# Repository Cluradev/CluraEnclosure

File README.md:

# CluraEnclosure

**The Clura Enclosure** is the 100% open-source, modular, and smart enclosure designed for desktop 3D printers. Developed with a focus on safety and air quality, it incorporates active filtration and smart sensors to enhance your 3D printing experience.

[Discord Community](https://discord.gg/dJDUmdvcgZ)

## Why We Built It

The project started with me (Fabrizio), an aerospace engineering student who wanted to print in his room without compromising his safety. In fact, it is widely documented that most 3D printer filaments emit VOCs and particulate matter, which can be harmful to health. I searched for a smart, affordable, open-source enclosure but couldn't find one, so I decided to build my own. 18 months of hard work later, here we are!

## Kits

Kickstarter orders are being fulfilled. Future kit batches are being planned, but nothing is finalized yet.

You can still build the enclosure today without waiting on us. Everything here is open source and the [Bill of Materials](Documentation/README.md) lists every part with soemtimes supplier links.

The original campaign page is still up for reference: [Kickstarter](https://www.kickstarter.com/projects/clura/enclosure)

## Documentation

All project documentation, including assembly manuals and Bills of Materials (BOM), will also be published on **CluraDocs**. If you're looking to assemble your own Clura Enclosure, that is the place to go. Note: CluraDocs is still a work in progress, we are always working on improving it. If you have any suggestions or feedback, please let us know!

Check it out here: [CluraDocs](https://docs.clura.dev)

## Key Features

- **Safety & Air Quality:** Dual-layer HEPA and carbon filtration system designed to capture VOCs and UFPs.
- **Smart Controls:** Integrated 4.3" touchscreen for real-time monitoring of temperature, humidity, and air quality.
- **Modular Design:** Fully customizable hardware and software modules.
- **Open Source:** 100% open source CAD files, firmware, and guides.

## Repository Structure

- `Documentation/`: Assembly manual and BOM.
- `Firmware/`: Firmware for the screen and the mainboard, plus the SD card files.
- `CAD/`: STEP models of the full enclosure, one per size (PE1, BE1, ME1).
- `PCBs/`: KiCad 9 sources for the mainboard and the sensorboard.
- `Production/`: Ready-to-use production files (laser cutting, extrusions, metal plates, PCB gerbers).
- `3D Printable Files/`: The `.3mf` files you print yourself.

In each folder there is a readme file with more info.

> For the printable parts, [CluraDocs](https://docs.clura.dev/the-build/preparations/printed-parts) has a picker that works out exactly which files and quantities your build needs.

## License

Every file in this repository is released under the **CC BY-NC (Creative Commons Attribution-NonCommercial)** license. 

For more details on the reasoning behind this choice, you can read our blog post: [The License - Clura Blog](https://www.clura.dev/blog/the-license)

---
*For more information, visit [clura.dev](https://www.clura.dev).*

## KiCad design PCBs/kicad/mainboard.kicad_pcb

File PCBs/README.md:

# Mainboard + Sensorboard

Open hardware KiCad 9 designs for a two-board set: an STM32F411-based **mainboard**
that handles power, control and I/O, and a companion **sensorboard** carrying the
gas/smoke sensing front end. The two connect over an RJ45 link.

## Boards

| | Mainboard | Sensorboard |
|---|---|---|
| Size | 120.05 × 90.05 mm | 73.04 × 50.07 mm |
| Copper layers | 4 (F.Cu, In1 GND, In2 VIN, B.Cu) | 2 (F.Cu, B.Cu) |
| Thickness | 1.6 mm | 1.6 mm |
| Placements | 174 | 22 |
| Revision | Rev-B | Rev-B |

### Mainboard

- **MCU** — STM32F411CEU6, 25 MHz HSE + 32.768 kHz LSE crystals, SWD header, BOOT jumper
- **Storage** — micro SD card slot, AT24CS64 I²C EEPROM
- **Power** — 12 V input via barrel jack / screw terminal, LM2596 switchers for 12 V and 5 V rails,
  SY8120B for 3V3, dedicated +5 V servo rail, fuse and reverse-protection diode
- **I/O** — RJ45 to the sensorboard, HX711 load-cell interface, PMS5003 particulate sensor header,
  three fan channels (60 mm, 140 mm, regulator fan) with MOSFET drive and tach/PWM,
  servo output, 5 V SSR terminal, WS2811 LED strip, buzzer, display header, DHT11, DIP + push switches
- **Protection** — PESD/BSD TVS arrays on the exposed interfaces

### Sensorboard

- MEMS smoke sensor, electrochemical smoke sensor and an optical channel
- LM317 (SOT-223) and SSP7901P33MR regulation
- WS2811 addressable LED
- RJ45 back to the mainboard, screw terminal sensor output, jumper-selectable options

## Repository layout

```
kicad/                  KiCad 9 source — open a .kicad_pro here
  mainboard.kicad_pro / .kicad_sch / .kicad_pcb
  sensorboard.kicad_pro / .kicad_sch / .kicad_pcb
  SensorBoard.kicad_sch    shared hierarchical sub-sheet
  power.kicad_sch          shared hierarchical sub-sheet
  3dmodels/                see note below
3d/mainboard.step          assembled 3D model
images/                    board renders
```

## Opening the projects

Both projects target **KiCad 9.0**. Open `kicad/mainboard.kicad_pro` or
`kicad/sensorboard.kicad_pro`. All symbols and footprints are cached inside the
`.kicad_sch` / `.kicad_pcb` files, so the boards render and plot correctly on a
stock KiCad install with no extra libraries.

A handful of symbols and footprints originate from custom libraries
(`custom_Library`, `custom`, `board`, `CustomFootprint`, `PESD5V0S1BA`,
`74HCT1G125GW`). Those libraries are not part of this repository, so KiCad will
report them as missing if you use *Update Symbols/Footprints from Library*. Normal
editing, plotting and DRC are unaffected.

## Manufacturing

Go to the production folder in the main repo.

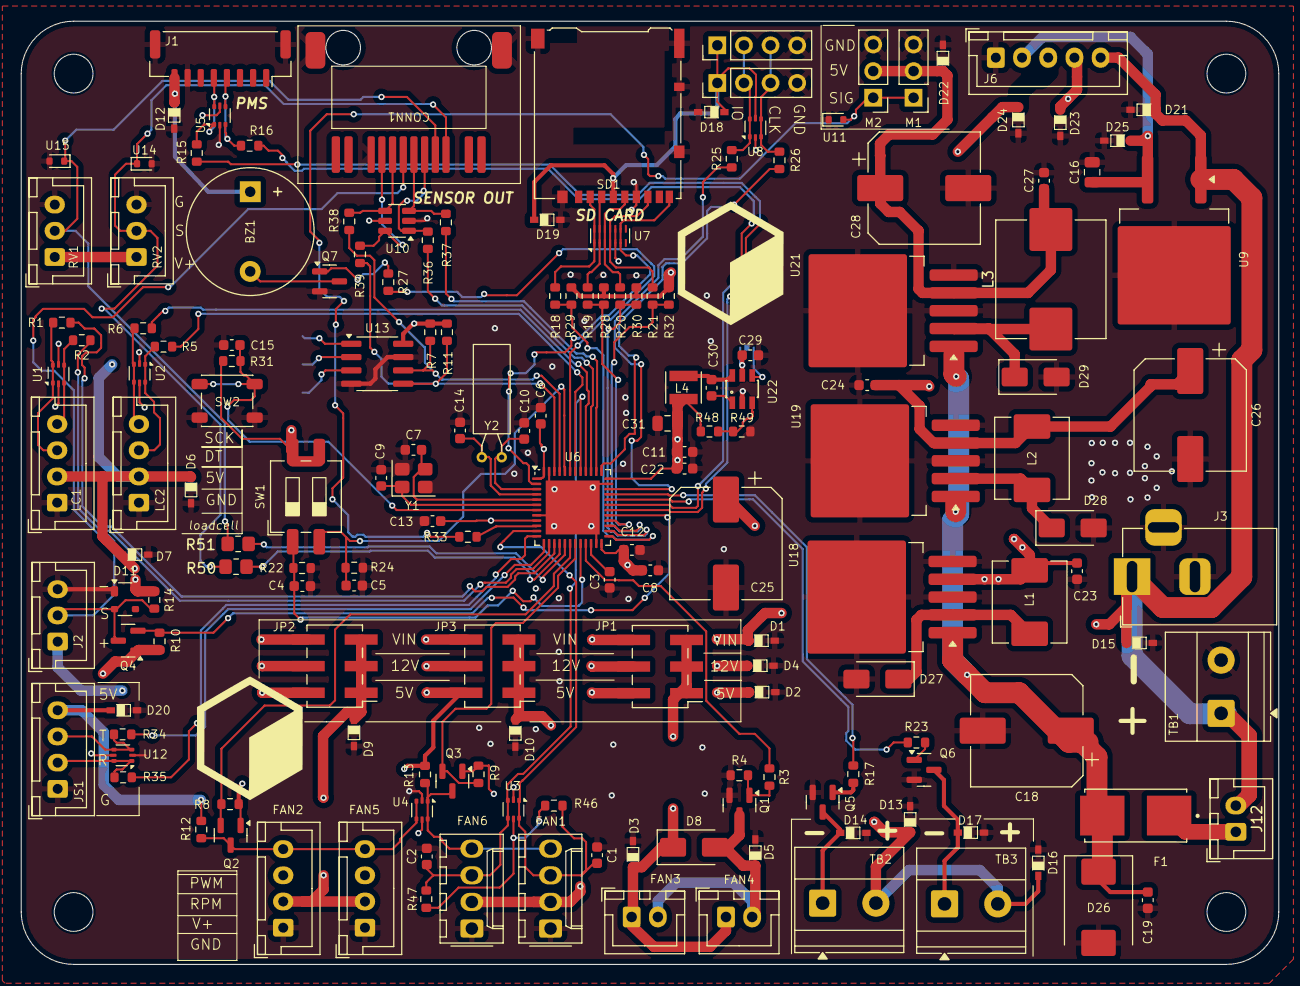
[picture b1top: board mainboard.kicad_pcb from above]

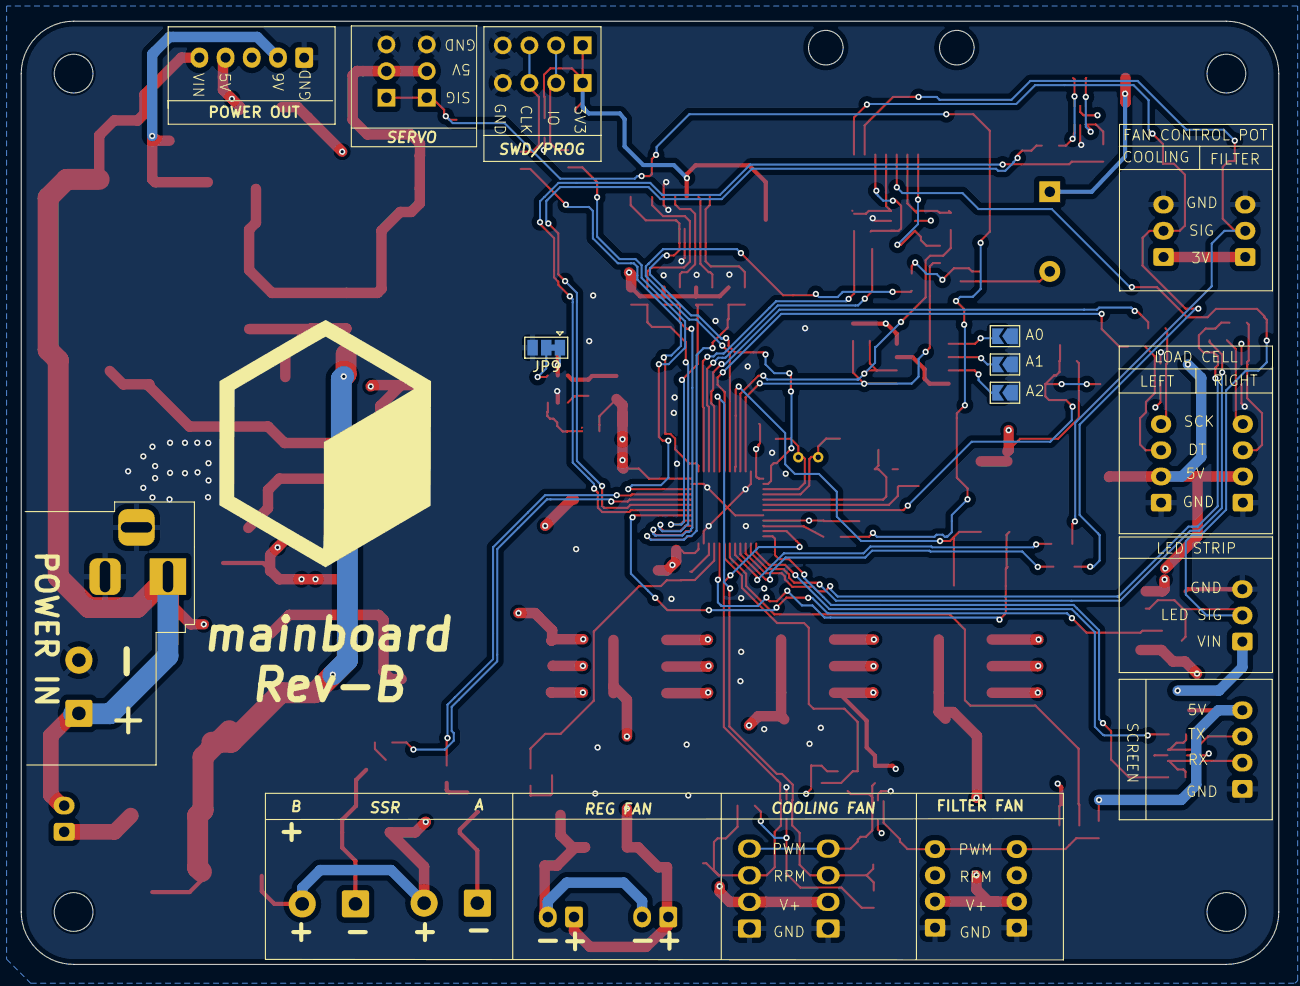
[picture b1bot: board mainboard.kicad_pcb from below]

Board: 4 copper layers, 120.0 x 90.0 mm, 174 parts (4 on the bottom side), 94 nets.

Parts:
BZ1: Buzzer; Buzzer_12x9.5RM7.6
C1, C2, C4, C5, C11, C12, C13, C15, C22, C23, C24, C27: 0.1uF; C_0603_1608Metric
C3: 2.2uF; C_0603_1608Metric
C6: 1uF; C_0603_1608Metric
C7, C9: 6pF; C_0603_1608Metric
C8: 10nF; C_0603_1608Metric
C10, C14: 15pF; C_0603_1608Metric
C16: 4.7uF; C_0805_2012Metric
C18: 4.7uF; CP_Elec_10x10.5
C19: 4.7uF; C_0603_1608Metric
C25, C26, C28: 470uF; CP_Elec_10x10.5
C29: 100n; C_0603_1608Metric
C30: 10n; C_0603_1608Metric
C31: 22u; C_0805_2012Metric
CONN1: RJ45_NEW
D1, D3, D5, D9, D10, D15, D21: BSD3A311V; SOD323
D2, D6, D7, D12, D13, D14, D16, D17, D20, D22, D23: PESD5V0S1UA; SOD323
D4, D25: PESD12VS1UA.; SOD323
D8: SS34; D_SMA
D11: PRTR5V0U2X; SOT-143
D18, D19, D24: PESD3V3L1BA; SOD323
D26: S6MC; D_SMC
D27, D28, D29: SS14; D_SMA
F1: 3A; FUSE_01550900M
FAN1, FAN6: 140mm_FAN; Molex_KK-254_AE-6410-04A_1x04_P2.54mm_Vertical
FAN2, FAN5: 60mm_FAN; JST_XH_B4B-XH-A_1x04_P2.50mm_Vertical
FAN3, FAN4: Fan; JST_XH_B2B-XH-A_1x02_P2.50mm_Vertical
H1, H2, H3, H4: MountingHole; MountingHole_3.7mm
J1: pms5003; JST_GH_SM08B-GHS-TB_1x08-1MP_P1.25mm_Horizontal
J2: LED Strip; JST_XH_B3B-XH-A_1x03_P2.50mm_Vertical
J3: POWER IN TERMINAL; BarrelJack_Horizontal
J4, J5: SWD HEADER; PinHeader_1x04_P2.54mm_Vertical
J6: Power_Out; JST_XH_B5B-XH-A_1x05_P2.50mm_Vertical
J12: SWITCH; JST_XH_B2B-XH-A_1x02_P2.50mm_Vertical
JP1: REG FAN JUMPER; PinHeader_2x03_P2.54mm_Vertical_SMD
JP2: 60MM FAN JUMPER; PinHeader_2x03_P2.54mm_Vertical_SMD
JP3: 140 MM FAN JUMPER; PinHeader_2x03_P2.54mm_Vertical_SMD
JP4, JP5, JP6: SolderJumper_2_Open; SolderJumper-2_P1.3mm_Open_TrianglePad1.0x1.5mm
JP9: JMP; SolderJumper-3_P1.3mm_Bridged12_Pad1.0x1.5mm
JS1: Screen; JST_XH_B4B-XH-A_1x04_P2.50mm_Vertical
L1, L2: 47uH; L_Chilisin_BMRx00060630
L3: 47uH; L_APV_APH1050
L4: 10uH/SFEK3015A-100M-HF; L_Neosid_SMS-ME3015
LC1, LC2: LOAD CELL AMP; JST_XH_B4B-XH-A_1x04_P2.50mm_Vertical
M1, M2: Motor_Servo; PinHeader_1x03_P2.54mm_Vertical
Q1: MOSFET-FAN; SOT-23
Q2, Q3, Q4: BSS138; SOT-23
Q5, Q6, Q7: SS8050; SOT-23
R1, R2, R3, R5, R6, R15, R16, R34, R35: 100R; R_0603_1608Metric
R4, R7, R11, R22, R24, R28, R29, R30, R31, R32, R46, R47: 10K; R_0603_1608Metric
R8, R9, R10: 10k; R_0603_1608Metric
R12, R13, R14: 470R; R_0603_1608Metric
R17, R23, R27: 220R; R_0603_1608Metric
R18, R19, R20, R21, R25, R26, R33, R36, R37, R38, R39: 22R; R_0603_1608Metric
R48: 100k; R_0603_1608Metric
R49: 22.1k; R_0603_1608Metric
R50, R51: 0R; R_0805_2012Metric_Pad1.20x1.40mm_HandSolder
RV1: F60; JST_XH_B3B-XH-A_1x03_P2.50mm_Vertical
RV2: F140; JST_XH_B3B-XH-A_1x03_P2.50mm_Vertical
SD1: Micro_SD_Card_Det1; microSD_HC_Hirose_DM3AT-SF-PEJM5
SW1: BOOT_JP; SW_DIP_SPSTx02_Slide_6.7x6.64mm_W8.61mm_P2.54mm_LowProfile
SW2: RESET_SW; SW_SPST_PTS647_Sx50
TB1: POWER; TerminalBlock_Phoenix_MKDS-1,5-2-5.08_1x02_P5.08mm_Horizont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
TB2: 5V SSR TERMINAL1; TerminalBlock_Phoenix_MKDS-1,5-2-5.08_1x02_P5.08mm_Horizont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
TB3: 5V SSR TERMINAL2; TerminalBlock_Phoenix_MKDS-1,5-2-5.08_1x02_P5.08mm_Horizont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
U1, U2, U3, U4, U5, U8, U12: USBLC6-2P6; SOT-666
U6: STM32F411CEUx; QFN-48-1EP_7x7mm_P0.5mm_EP5.15x5.15mm
U7: TPD6E05U06RVZ; Texas_R-PUSON-N14
U9: L7809; TO-263-2
U10: USBLC6-4SC6; SOT-23-6
U11, U14, U15: BNTPD1E05U06DYAR; D_SOD-523
U13: AT24CS64-SSHM; SOIC-8_3.9x4.9mm_P1.27mm
U18, U21: LM2596S-5; TO-263-5_TabPin3
U19: LM2596S-12; TO-263-5_TabPin3
U22: SY8120B; SOT23-6
Y1: 25MHz; Crystal_SMD_3225-4Pin_3.2x2.5mm
Y2: 32.768KHz; Crystal_C38-LF_D3.0mm_L8.0mm_Horizontal

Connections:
+3.3V: C6.1, C8.1, C11.1, C12.1, C13.1, C22.1, C31.1, D18.1, D19.1, D24.1, J4.1, J5.1, L4.2, Q2.1 (G), Q3.1 (G), Q4.1 (G), R7.1, R8.1, R9.1, R10.1, R11.1, R28.1, R29.1, R30.1, R31.1, R32.1, R46.1, R47.1, R48.1, RV1.1, RV2.1, SD1.4 (VDD), SW1.3, SW1.4, U1.5 (VBUS), U2.5 (VBUS), U3.5 (VBUS), U5.5 (VBUS), U6.1 (VBAT), U6.9 (VDDA), U6.24 (VDD), U6.36 (VDD), U6.48 (VDD), U8.5 (VBUS), U10.5 (VBUS), U12.5 (VBUS), U13.8 (VCC)
+5V: BZ1.1 (+), C23.1, C25.1, D2.1, D6.1, D7.1, D11.4 (VCC), D12.1, D13.1, D16.1, D20.1, D23.1, J1.8 (VCC), J6.4, JP1.2, JP2.2, JP3.2, JS1.4, L1.2, LC1.2 (VCC), LC2.2 (VCC), R12.1, R13.1, R14.1, TB2.2, TB3.2, U4.5 (VBUS), U18.4 (FB)
+5VSERVO: C27.1, C28.1, D22.1, L3.2, M1.2 (+), M2.2 (+), U21.4 (FB)
+9V: C16.1, D25.1, J6.2, U9.3 (OUT)
+12V: C24.1, C26.1, C29.1, D4.1, JP1.4, JP2.4, JP3.4, JP9.1 (A), L2.2, U19.4 (FB), U22.5 (IN)
/12-24V_IN: D1.1, D15.1, D21.1, J2.1, J3.1, J6.5, J12.2, JP1.6, JP2.6, JP3.6, TB1.1, U9.1 (IN)
/ALARM: R36.2, U6.39 (PB3)
/BOOT0: C5.1, R24.1, SW1.2, U6.44 (BOOT0)
/BOOT1: C4.1, R22.1, SW1.1, U6.20 (PB2)
/BUZZER: R27.2, U6.43 (PB7)
/CLK: R20.1, R30.2, U6.26 (PB13)
/CS: R18.1, R29.2, U6.25 (PB12)
/DET: SD1.9 (DET_B), U6.2 (PC13), U7.6 (NC), U7.9 (D3+)
/F60_HS: FAN2.4 (PWM), FAN5.4 (PWM), Q2.3 (D), R12.2, U4.3 (I/O2), U4.4 (I/O2)
/F60_LS: Q2.2 (S), R8.2, U6.18 (PB0)
/F140_HS: FAN1.4 (PWM), FAN6.4 (PWM), Q3.3 (D), R13.2, U4.1 (I/O1), U4.6 (I/O1)
/F140_LS: Q3.2 (S), R9.2, U6.19 (PB1)
/HX1DT: R1.1, U6.15 (PA5)
/HX1_SCK: R2.1, U6.14 (PA4)
/HX2DT: R5.1, U6.42 (PB6)
/HX2_SCK: R6.1, U6.40 (PB4)
/LED_LOW_SIDE: Q4.2 (S), R10.2, U6.29 (PA8)
/MEMS_AOUT: CONN1.1, R50.2, RV2.2, U14.1 (I/O)
/MISO: R21.1, R32.2, U6.27 (PB14)
/MOSI: R19.1, R28.2, U6.28 (PB15)
/MQ2: CONN1.2, R51.2, RV1.2, U15.1 (I/O)
/MUTE: R37.2, U6.38 (PA15)
/NRST: C15.1, R31.2, SW2.1, U6.7 (NRST)
/PA13: R25.1, U6.34 (PA13)
/PA14: R26.1, U6.37 (PA14)
/PH0: C7.2, U6.5 (PH0), Y1.3
/PH1: C9.2, U6.6 (PH1), Y1.1
/PMS_RX: R15.1, U6.30 (PA9)
/PMS_TX: R16.1, U6.31 (PA10)
/PWM_REG: R3.1, U6.21 (PB10)
/SCL: R7.2, R38.2, U6.45 (PB8), U13.6 (SCL)
/SCREEN_RX: R35.1, U6.12 (PA2)
/SCREEN_TX: R34.1, U6.13 (PA3)
/SDA: R11.2, R39.2, U6.46 (PB9), U13.5 (SDA)
/SERV0: R33.1, U6.10 (PA0)
/SSR1: R17.2, U6.33 (PA12)
/SSR2: R23.2, U6.32 (PA11)
/Sensor Board/GND: C18.2, C19.2
/TACH1: C1.2, FAN1.3 (Tacho), R46.2, U3.1 (I/O1), U3.6 (I/O1), U6.11 (PA1)
/TACH2: C2.1, FAN6.3 (Tacho), R47.2, U3.3 (I/O2), U3.4 (I/O2), U6.41 (PB5)
/WS2811: CONN1.5, D11.2 (I/O1), J2.2, Q4.3 (D), R14.2
/XTAL1A: C10.2, U6.3 (PC14), Y2.1
/XTAL1B: C14.2, U6.4 (PC15), Y2.2
/power/VIN: D26.1 (K), F1.2, U18.1 (VIN), U19.1 (VIN), U21.1 (VIN)
GND: C1.1, C2.2, C3.2, C4.2, C5.2, C6.2, C7.1, C8.2, C9.1, C10.1, C11.2, C12.2, C13.2, C14.1, C15.2, C16.2, C22.2, C23.2, C24.2, C25.2, C26.2, C27.2, C28.2, C29.2, C31.2, CONN1.8, CONN1.SH, D1.2, D2.2, D3.2, D4.2, D5.2, D6.2, D7.2, D9.2, D10.2, D11.1 (GND), D12.2, D13.2, D14.2, D15.2, D16.2, D17.2, D18.2, D19.2, D20.2, D21.2, D22.2, D23.2, D24.2, D25.2, D26.2 (A), D27.2 (A), D28.2 (A), D29.2 (A), FAN1.1 (-), FAN2.1 (-), FAN5.1 (-), FAN6.1 (-), J1.7 (GND), J1.MP, J2.3, J3.2, J3.3, J4.4, J5.4, J6.1, JP4.1 (A), JP5.1 (A), JP6.1 (A), JP9.3 (B), JS1.1, LC1.1 (GND), LC2.1 (GND), M1.3 (-), M2.3 (-), Q1.2 (S), Q5.2 (E), Q6.2 (E), Q7.2 (E), R4.1, R22.2, R24.2, R49.2, RV1.3, RV2.3, SD1.6 (VSS), SD1.10 (DET_A), SD1.11 (SHIELD), SW2.2, TB1.2, U1.2 (GND), U2.2 (GND), U3.2 (GND), U4.2 (GND), U5.2 (GND), U6.8 (VSSA), U6.23 (VSS), U6.35 (VSS), U6.47 (VSS), U6.49 (VSS), U7.5 (GND), U7.10 (GND), U8.2 (GND), U9.2 (GND), U10.2 (GND), U11.1 (I/O), U12.2 (GND), U13.4 (GND), U13.7 (WP), U14.2 (GND), U15.2 (GND), U18.3 (GND), U18.5 (~ON/OFF), U19.3 (GND), U19.5 (~ON/OFF), U21.3 (GND), U21.5 (~ON/OFF), U22.2 (GND), Y1.2, Y1.4
unnamed: BZ1.2 (-), Q7.3 (C)
unnamed: D5.1, D8.2 (A), FAN3.2 (-), FAN4.2 (-), Q1.3 (D)
unnamed: D3.1, D8.1 (K), FAN3.1 (+), FAN4.1 (+), JP1.1, JP1.3, JP1.5
unnamed: D27.1 (K), L1.1, U18.2 (OUT)
unnamed: D28.1 (K), L2.1, U19.2 (OUT)
unnamed: D29.1 (K), L3.1, U21.2 (OUT)
unnamed: D10.1, FAN1.2 (+), FAN6.2 (+), JP3.1, JP3.3, JP3.5
unnamed: D9.1, FAN2.2 (+), FAN5.2 (+), JP2.1, JP2.3, JP2.5
unnamed: J1.5 (RX), R15.2, U5.1 (I/O1), U5.6 (I/O1)
unnamed: J1.4 (TX), R16.2, U5.3 (I/O2), U5.4 (I/O2)
unnamed: J4.2, J5.2, R25.2, U8.1 (I/O1), U8.6 (I/O1)
unnamed: J4.3, J5.3, R26.2, U8.3 (I/O2), U8.4 (I/O2)
unnamed: F1.1, J12.1
unnamed: JP4.2 (B), U13.1 (A0)
unnamed: JP5.2 (B), U13.2 (A1)
unnamed: JP6.2 (B), U13.3 (A2)
unnamed: JP9.2 (C), U22.4 (EN)
unnamed: JS1.2, R35.2, U12.1 (I/O1), U12.6 (I/O1)
unnamed: JS1.3, R34.2, U12.3 (I/O2), U12.4 (I/O2)
unnamed: LC1.3 (DT), R1.2, U1.1 (I/O1), U1.6 (I/O1)
unnamed: LC1.4 (SCK), R2.2, U1.3 (I/O2), U1.4 (I/O2)
unnamed: LC2.3 (DT), R5.2, U2.1 (I/O1), U2.6 (I/O1)
unnamed: LC2.4 (SCK), R6.2, U2.3 (I/O2), U2.4 (I/O2)
unnamed: M1.1 (PWM), M2.1 (PWM), R33.2, U11.2 (GND)
unnamed: Q1.1 (G), R3.2, R4.2
unnamed: Q5.1 (B), R17.1
unnamed: D14.1, Q5.3 (C), TB2.1
unnamed: Q6.1 (B), R23.1
unnamed: D17.1, Q6.3 (C), TB3.1
unnamed: Q7.1 (B), R27.1
unnamed: R20.2, SD1.5 (CLK), U7.3 (NC), U7.12 (D2+)
unnamed: R19.2, SD1.3 (CMD), U7.2 (NC), U7.13 (D1-)
unnamed: R21.2, SD1.7 (DAT0), U7.4 (NC), U7.11 (D2-)
unnamed: R18.2, SD1.2 (DAT3/CD), U7.1 (NC), U7.14 (D1+)
unnamed: R50.1, U6.16 (PA6)
unnamed: R51.1, U6.17 (PA7)
unnamed: C3.1, U6.22 (VCAP1)
unnamed: CONN1.3, R36.1, U10.1 (I/O1)
unnamed: CONN1.4, R37.1, U10.3 (I/O2)
unnamed: CONN1.6, R38.1, U10.4 (I/O3)
unnamed: CONN1.7, R39.1, U10.6 (I/O4)
unnamed: C30.1, U22.1 (BS)
unnamed: R48.2, R49.1, U22.3 (FB)
unnamed: C30.2, L4.1, U22.6 (LX)

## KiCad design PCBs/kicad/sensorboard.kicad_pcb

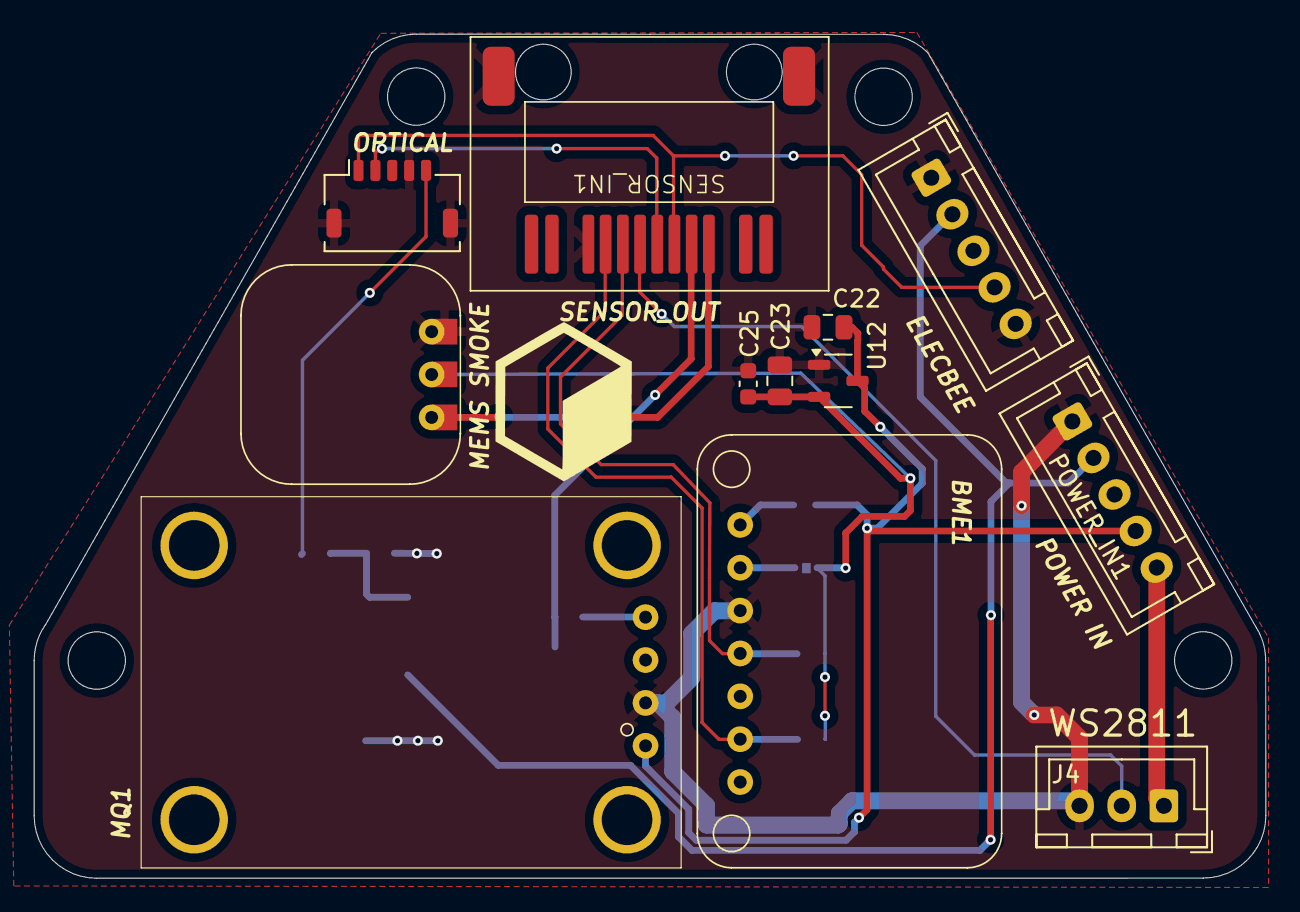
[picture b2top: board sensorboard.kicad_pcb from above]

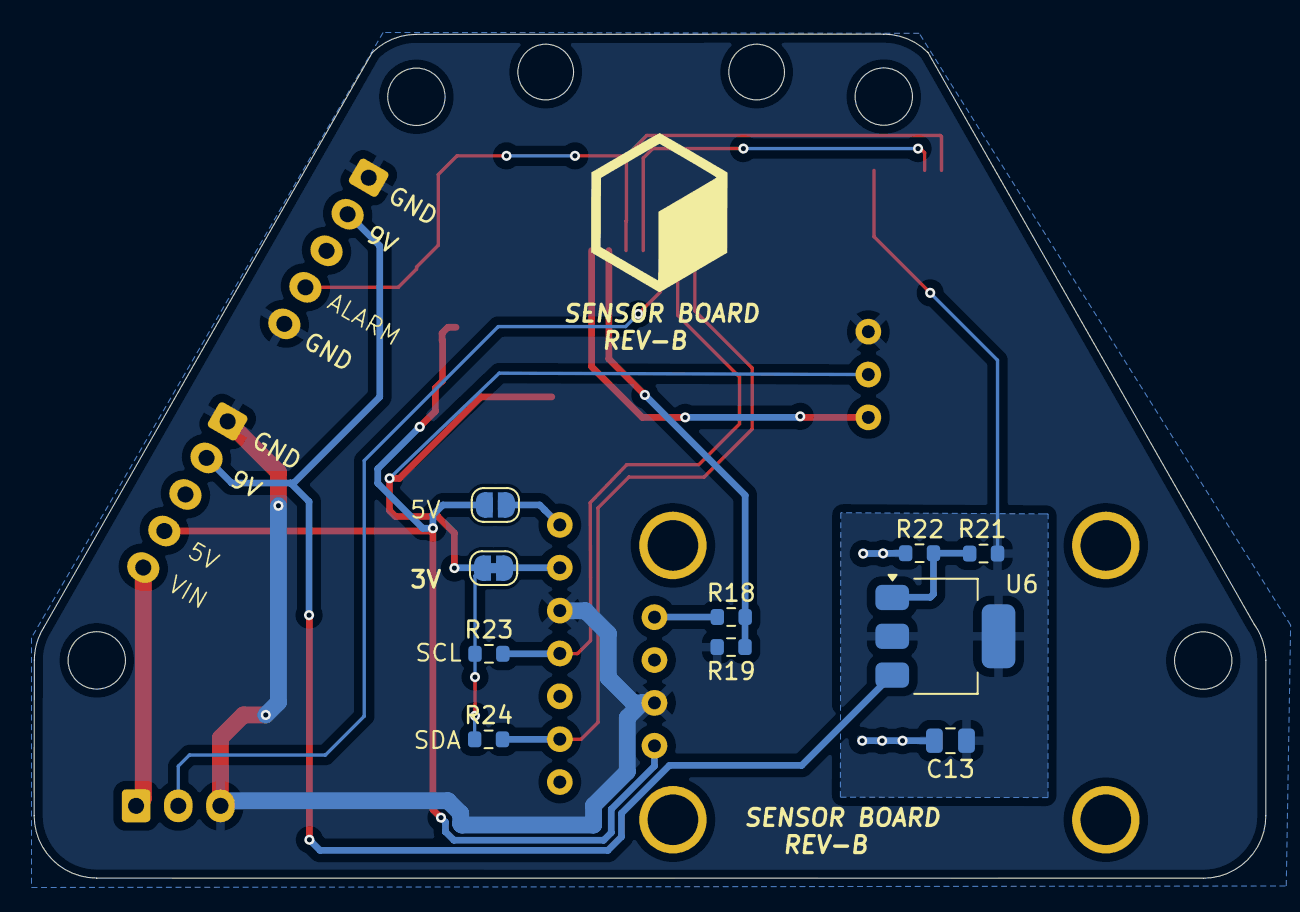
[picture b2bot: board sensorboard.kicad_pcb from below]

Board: 2 copper layers, 73.0 x 50.0 mm, 22 parts (10 on the bottom side), 17 nets.

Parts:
BME1: Bme680
C13, C22, C23: 4.7uF; C_0805_2012Metric
C25: 0.1uF; C_0603_1608Metric
ELECBEE1: Elec_Smoke; JST_XH_B5B-XH-A_1x05_P2.50mm_Vertical
J4: WS2811; JST_XH_B3B-XH-A_1x03_P2.50mm_Vertical
JP1: Jumper_2_Open; SolderJumper-2_P1.3mm_Open_RoundedPad1.0x1.5mm
JP2: Jumper_2_Bridged; SolderJumper-2_P1.3mm_Bridged_RoundedPad1.0x1.5mm
MEMS_SMOKE1: MEMS_Smoke; MEMS_SMOKE
MQ1: MQ2-MODULE
OPTICAL_SMOKE1: JST_SHL_SM05B-SHLS-TF_1x05-1MP_P1.00mm_Horizontal
POWER_IN1: Power_in; JST_XH_B5B-XH-A_1x05_P2.50mm_Vertical
R18: 5k; R_0603_1608Metric
R19: 10k; R_0603_1608Metric
R21: 2.2k; R_0603_1608Metric
R22: 4.3k; R_0603_1608Metric
R23, R24: 10K; R_0603_1608Metric
SENSOR_IN1: SENSOR_OUT; RJ45_NEW
U6: LM317_SOT-223; SOT-223-3_TabPin2
U12: SSP7901P33MR; SOT-23-3

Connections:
/Sensor Board/3.7V: C13.1, OPTICAL_SMOKE1.5 (VCC), R21.1, U6.2 (VO)
/Sensor Board/3V: C23.1, C25.1, JP2.2 (B), MEMS_SMOKE1.2 (VCC), R23.1, R24.1, U12.2 (VOUT)
/Sensor Board/5V: C22.1, JP1.1 (A), MQ1.1 (VCC), POWER_IN1.4, U12.3 (VIN)
/Sensor Board/9V: ELECBEE1.2 (+9V), POWER_IN1.2, U6.3 (VI)
/Sensor Board/12-24V_IN: J4.1, POWER_IN1.5
/Sensor Board/ALARM: ELECBEE1.4 (CO), OPTICAL_SMOKE1.1 (ALARM), SENSOR_IN1.3
/Sensor Board/GND: BME1.3 (GND), C13.2, C22.2, C23.2, C25.2, ELECBEE1.1 (GND), ELECBEE1.5 (NC), J4.3, MEMS_SMOKE1.3 (GND), MQ1.2 (GND), OPTICAL_SMOKE1.4 (GND), OPTICAL_SMOKE1.MP, POWER_IN1.1, R19.2, R22.2, SENSOR_IN1.8, SENSOR_IN1.SH, U12.1 (GND)
/Sensor Board/MEMS_AOUT: MEMS_SMOKE1.1 (A), SENSOR_IN1.1
/Sensor Board/MQ2_DO: R18.2, R19.1, SENSOR_IN1.2
/Sensor Board/MUTE: OPTICAL_SMOKE1.2 (MUTE), SENSOR_IN1.4
/Sensor Board/SCL: BME1.4 (SCK), R23.2, SENSOR_IN1.6
/Sensor Board/SDA: BME1.6 (SDI), R24.2, SENSOR_IN1.7
/Sensor Board/WS2811: J4.2, SENSOR_IN1.5
unnamed: BME1.2 (3V), JP2.1 (A)
unnamed: BME1.1 (VIN), JP1.2 (B)
unnamed: MQ1.4 (AO), R18.1
unnamed: R21.2, R22.1, U6.1 (ADJ)

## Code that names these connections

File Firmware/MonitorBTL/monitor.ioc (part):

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Mcu.Name=STM32F411C(C-E)Ux
Mcu.Package=UFQFPN48
Mcu.UserName=STM32F411CEUx
PA0-WKUP.GPIOParameters=GPIO_Label
PA0-WKUP.GPIO_Label=SERVO
PA0-WKUP.Signal=S_TIM5_CH1
PA1.GPIOParameters=GPIO_PuPd,GPIO_Label,GPIO_ModeDefaultEXTI
PA1.GPIO_Label=TACHO_A
PA1.GPIO_ModeDefaultEXTI=GPIO_MODE_IT_FALLING
PA1.GPIO_PuPd=GPIO_PULLUP
PA1.Signal=GPXTI1
PA10.GPIOParameters=GPIO_Label
PA10.GPIO_Label=PMS_TX
PA10.Mode=Asynchronous
PA10.Signal=USART1_RX
PA11.GPIOParameters=GPIO_Label
PA11.GPIO_Label=SSR2
PA11.Signal=GPIO_Output
PA12.GPIOParameters=GPIO_Label
PA12.GPIO_Label=SSR1
PA12.Signal=GPIO_Output
PA13.Mode=Serial_Wire
PA13.Signal=SYS_JTMS-SWDIO
PA14.Mode=Serial_Wire
PA14.Signal=SYS_JTCK-SWCLK
PA15.GPIOParameters=GPIO_Label
PA15.GPIO_Label=MUTE
PA15.Signal=GPIO_Output
PA2.GPIOParameters=GPIO_Label
PA2.GPIO_Label=SCREEN_RX
PA2.Mode=Asynchronous
PA2.Signal=USART2_TX
PA3.GPIOParameters=GPIO_Label
PA3.GPIO_Label=SCREEN_TX
PA3.Mode=Asynchronous
PA3.Signal=USART2_RX
PA4.GPIOParameters=GPIO_Label
PA4.GPIO_Label=HX1SCK
PA4.Signal=GPIO_Output
PA5.GPIOParameters=GPIO_PuPd,GPIO_Label
PA5.GPIO_Label=HX1DT
PA5.GPIO_PuPd=GPIO_PULLUP
PA5.Signal=GPIO_Input
PA6.GPIOParameters=GPIO_Label
PA6.GPIO_Label=MEMS_SMOKE
PA6.Signal=ADCx_IN6
PA7.GPIOParameters=GPIO_Label
PA7.GPIO_Label=MQ2
PA7.Signal=ADCx_IN7
PA8.GPIOParameters=GPIO_Label
PA8.GPIO_Label=LED_PIN
PA8.Signal=S_TIM1_CH1
PA9.GPIOParameters=GPIO_Label
PA9.GPIO_Label=PMS_RX
PA9.Mode=Asynchronous
PA9.Signal=USART1_TX
PB0.GPIOParameters=GPIO_Label
PB0.GPIO_Label=pwm_60
PB0.Signal=S_TIM3_CH3
PB1.GPIOParameters=GPIO_Label
PB1.GPIO_Label=pwm_140
PB1.Signal=S_TIM3_CH4
PB10.GPIOParameters=GPIO_Label
PB10.GPIO_Label=pwm_reg
PB10.Signal=S_TIM2_CH3
PB12.GPIOParameters=GPIO_Label
PB12.GPIO_Label=CS
PB12.Signal=GPIO_Output
PB13.GPIOParameters=GPIO_PuPd,GPIO_Label
PB13.GPIO_Label=CLK
PB13.GPIO_PuPd=GPIO_PULLUP
PB13.Mode=Full_Duplex_Master
PB13.Signal=SPI2_SCK
PB14.GPIOParameters=GPIO_PuPd,GPIO_Label
PB14.GPIO_Label=MISO
PB14.GPIO_PuPd=GPIO_PULLUP
PB14.Mode=Full_Duplex_Master
PB14.Signal=SPI2_MISO
PB15.GPIOParameters=GPIO_PuPd,GPIO_Label
PB15.GPIO_Label=MOSI
PB15.GPIO_PuPd=GPIO_PULLUP
PB15.Mode=Full_Duplex_Master
PB15.Signal=SPI2_MOSI
PB3.GPIOParameters=GPIO_PuPd,GPIO_Label
PB3.GPIO_Label=ALARM
PB3.GPIO_PuPd=GPIO_PULLUP
PB3.Signal=GPIO_Input
PB4.GPIOParameters=GPIO_Label
PB4.GPIO_Label=HX2SCK
PB4.Signal=GPIO_Output
PB5.GPIOParameters=GPIO_PuPd,GPIO_Label,GPIO_ModeDefaultEXTI
PB5.GPIO_Label=TACHO_B
PB5.GPIO_ModeDefaultEXTI=GPIO_MODE_IT_FALLING
PB5.GPIO_PuPd=GPIO_PULLUP
PB5.Signal=GPXTI5
PB6.GPIOParameters=GPIO_PuPd,GPIO_Label
PB6.GPIO_Label=HX2DT
PB6.GPIO_PuPd=GPIO_PULLUP
PB6.Signal=GPIO_Input
PB7.GPIOParameters=GPIO_Label
PB7.GPIO_Label=BUZZER
PB7.Signal=GPIO_Output
PB8.GPIOParameters=GPIO_Label
PB8.GPIO_Label=SCL
PB8.Mode=I2C
PB8.Signal=I2C1_SCL
PB9.GPIOParameters=GPIO_Label
PB9.GPIO_Label=SDA
PB9.Mode=I2C
PB9.Signal=I2C1_SDA
PC13-ANTI_TAMP.GPIOParameters=GPIO_Label
PC13-ANTI_TAMP.GPIO_Label=DET
PC13-ANTI_TAMP.Signal=GPIO_Input
RCC.HSE_VALUE=25000000
RCC.SYSCLKFreq_VALUE=100000000
RCC.SYSCLKSource=RCC_SYSCLKSOURCE_PLLCLK
board=custom

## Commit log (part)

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2026-01-04 First Setup
2026-01-04 License
2026-01-13 Upload files with LFS for large STEP files
2026-02-09 ReadmeUpdate
2026-02-09 Readme Update 2
2026-02-09 Readme Update 3
2026-02-28 Kickstarter launch
2026-03-02 Readme Update 4
2026-06-11 Fix CluraDocs URL
